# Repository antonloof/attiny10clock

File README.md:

# attiny10clock
How to not make a clock. 
test

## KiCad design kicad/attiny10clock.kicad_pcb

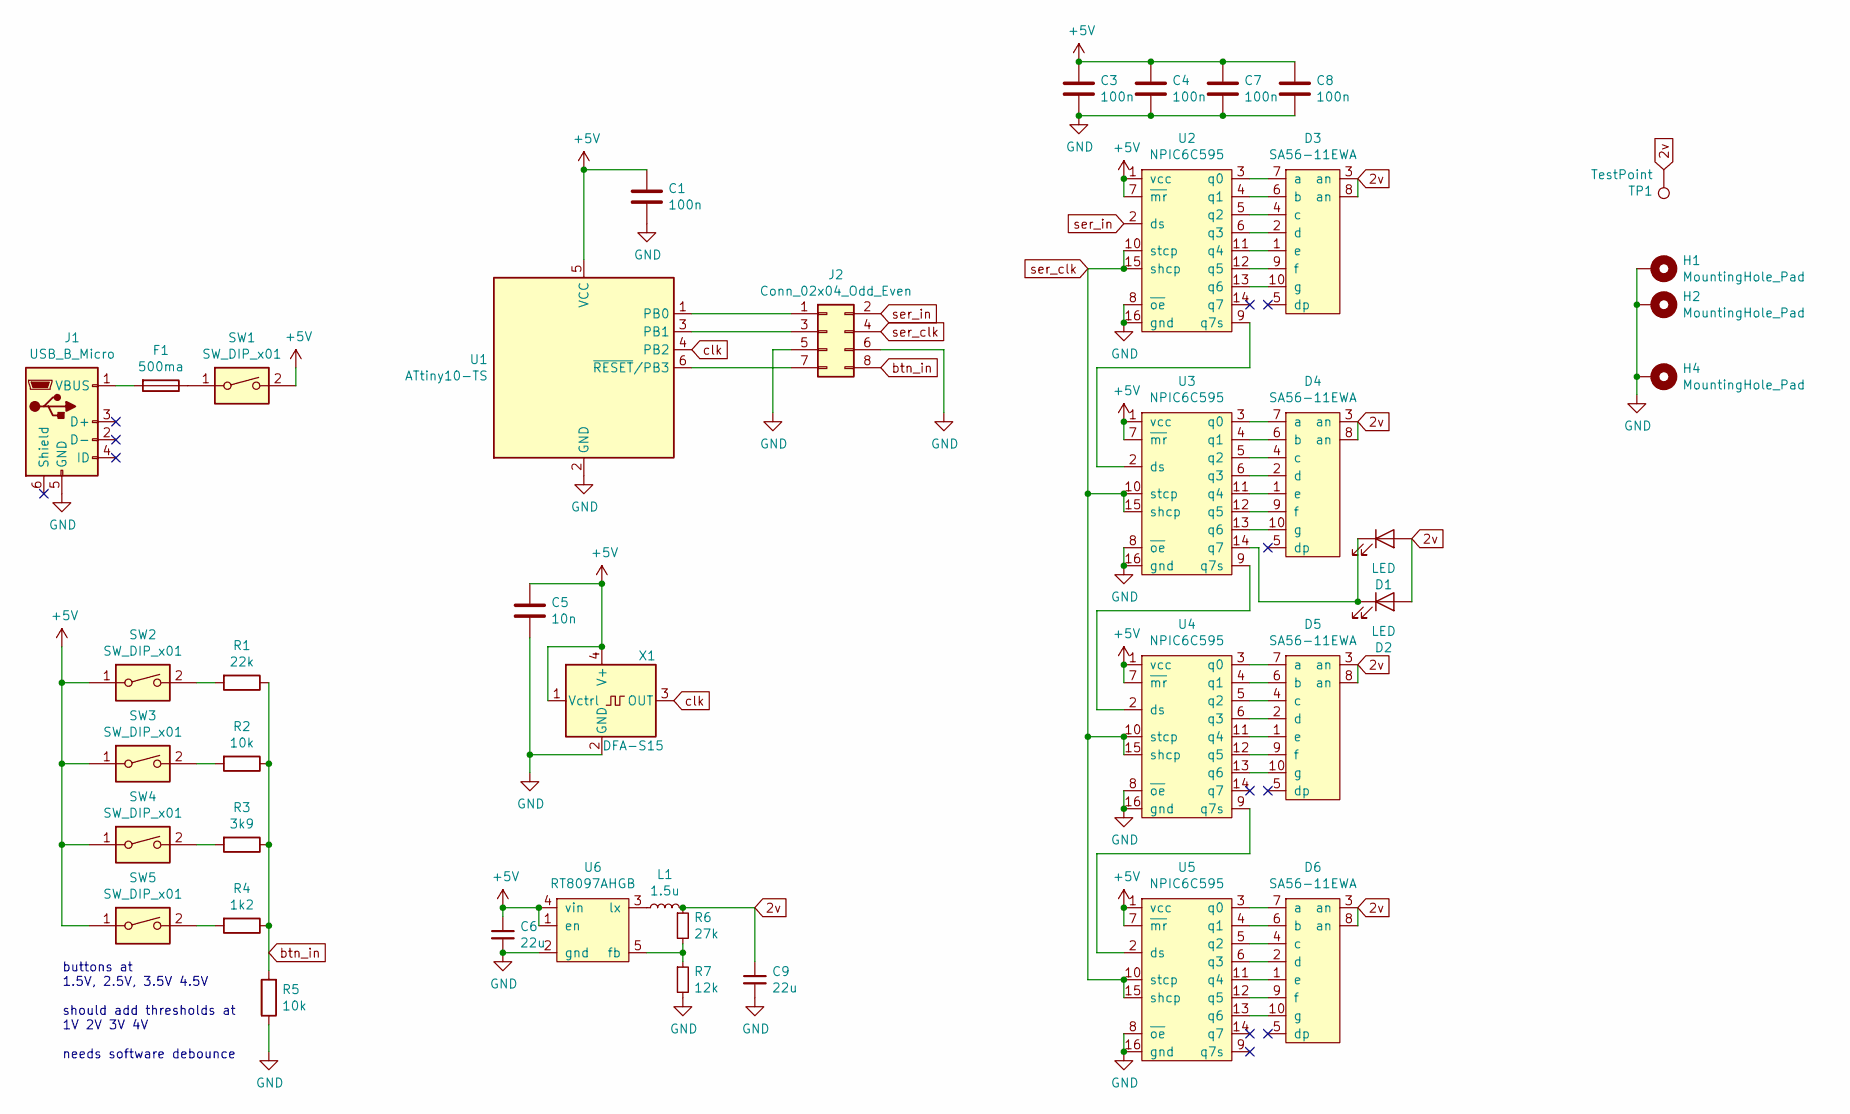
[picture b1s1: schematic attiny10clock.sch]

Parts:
C1, C3, C4, C7, C8: 100n; C_0805_2012Metric_Pad1.15x1.40mm_HandSolder
C5: 10n; C_0805_2012Metric_Pad1.15x1.40mm_HandSolder
C6, C9: 22u; C_0805_2012Metric_Pad1.15x1.40mm_HandSolder
D1, D2: LED; LED_D5.0mm
D3, D4, D5, D6: SA56-11EWA; DIP-10_600_ELL
F1: 500ma; Fuse_1206_3216Metric_Pad1.42x1.75mm_HandSolder
H1, H2, H4: MountingHole_Pad; MountingHole_2.2mm_M2_Pad
J1: USB_B_Micro; USB_MICRO_10118193-0001LF
J2: Conn_02x04_Odd_Even; PinHeader_2x04_P2.54mm_Vertical
L1: 1.5u; L_Wuerth_WE-PD-Typ-7345
R1: 22k; R_0603_1608Metric_Pad1.05x0.95mm_HandSolder
R2, R5: 10k; R_0603_1608Metric_Pad1.05x0.95mm_HandSolder
R3: 3k9; R_0603_1608Metric_Pad1.05x0.95mm_HandSolder
R4: 1k2; R_0603_1608Metric_Pad1.05x0.95mm_HandSolder
R6: 27k; R_0603_1608Metric_Pad1.05x0.95mm_HandSolder
R7: 12k; R_0603_1608Metric_Pad1.05x0.95mm_HandSolder
SW1: SW_DIP_x01; PinHeader_1x02_P2.54mm_Vertical
SW2, SW3, SW4, SW5: SW_DIP_x01; SW_Cherry_MX_1.00u_Plate
TP1: TestPoint; TestPoint_Pad_D2.0mm
U1: ATtiny10-TS; SOT-23-6
U2, U3, U4, U5: NPIC6C595; TSSOP-16_4.4x5mm_P0.65mm
U6: RT8097AHGB; SOT-23-5_HandSoldering
X1: DFA-S15; ASFLK

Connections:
2v: C9.1, D1.2 (A), D2.2 (A), D3.3 (an), D3.8 (an), D4.3 (an), D4.8 (an), D5.3 (an), D5.8 (an), D6.3 (an), D6.8 (an), L1.2, R6.1, TP1.1; also elsewhere on the board
+5V: C1.1, C3.1, C4.1, C5.1, C6.1, C7.1, C8.1, SW1.2, SW2.1, SW3.1, SW4.1, SW5.1, U1.5 (VCC), U2.1 (vcc), U2.7 (~mr), U3.1 (vcc), U3.7 (~mr), U4.1 (vcc), U4.7 (~mr), U5.1 (vcc), U5.7 (~mr), U6.1 (en), U6.4 (vin), X1.1 (Vctrl), X1.4 (V+)
GND: C1.2, C3.2, C4.2, C5.2, C6.2, C7.2, C8.2, C9.2, H1.1, H2.1, H4.1, J1.5 (GND), J2.5, J2.6, R5.1, R7.2, U1.2 (GND), U2.8 (~oe), U2.16 (gnd), U3.8 (~oe), U3.16 (gnd), U4.8 (~oe), U4.16 (gnd), U5.8 (~oe), U5.16 (gnd), U6.2 (gnd), X1.2 (GND)
unnamed: D1.1 (K), D2.1 (K), U3.14 (q7)
unnamed: D3.1 (e), U2.11 (q4)
unnamed: D3.2 (d), U2.6 (q3)
unnamed: D3.4 (c), U2.5 (q2)
unnamed: D3.6 (b), U2.4 (q1)
unnamed: D3.7 (a), U2.3 (q0)
unnamed: D3.9 (f), U2.12 (q5)
unnamed: D3.10 (g), U2.13 (q6)
unnamed: D4.1 (e), U3.11 (q4)
unnamed: D4.2 (d), U3.6 (q3)
unnamed: D4.4 (c), U3.5 (q2)
unnamed: D4.6 (b), U3.4 (q1)
unnamed: D4.7 (a), U3.3 (q0)
unnamed: D4.9 (f), U3.12 (q5)
unnamed: D4.10 (g), U3.13 (q6)
unnamed: D5.1 (e), U4.11 (q4)
unnamed: D5.2 (d), U4.6 (q3)
unnamed: D5.4 (c), U4.5 (q2)
unnamed: D5.6 (b), U4.4 (q1)
unnamed: D5.7 (a), U4.3 (q0)
unnamed: D5.9 (f), U4.12 (q5)
unnamed: D5.10 (g), U4.13 (q6)
unnamed: D6.1 (e), U5.11 (q4)
unnamed: D6.2 (d), U5.6 (q3)
unnamed: D6.4 (c), U5.5 (q2)
unnamed: D6.6 (b), U5.4 (q1)
unnamed: D6.7 (a), U5.3 (q0)
unnamed: D6.9 (f), U5.12 (q5)
unnamed: D6.10 (g), U5.13 (q6)
unnamed: F1.1, SW1.1
unnamed: F1.2, J1.1 (VBUS)
unnamed: J2.1, U1.1 (PB0)
unnamed: J2.3, U1.3 (PB1)
unnamed: J2.7, U1.6 (~RESET~/PB3)
unnamed: L1.1, U6.3 (lx)
unnamed: R1.2, SW2.2
unnamed: R2.2, SW3.2
unnamed: R3.2, SW4.2
unnamed: R4.2, SW5.2
unnamed: R6.2, R7.1, U6.5 (fb)
unnamed: U2.9 (q7s), U3.2 (ds)
unnamed: U3.9 (q7s), U4.2 (ds)
unnamed: U4.9 (q7s), U5.2 (ds)
btn_in: J2.8, R1.1, R2.1, R3.1, R4.1, R5.2
clk: U1.4 (PB2), X1.3 (OUT)
ser_clk: J2.4, U2.10 (stcp), U2.15 (shcp), U3.10 (stcp), U3.15 (shcp), U4.10 (stcp), U4.15 (shcp), U5.10 (stcp), U5.15 (shcp)
ser_in: J2.2, U2.2 (ds)

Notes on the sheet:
buttons at 1.5V, 2.5V, 3.5V 4.5V should add thresholds at 1V 2V 3V 4V needs software debounce

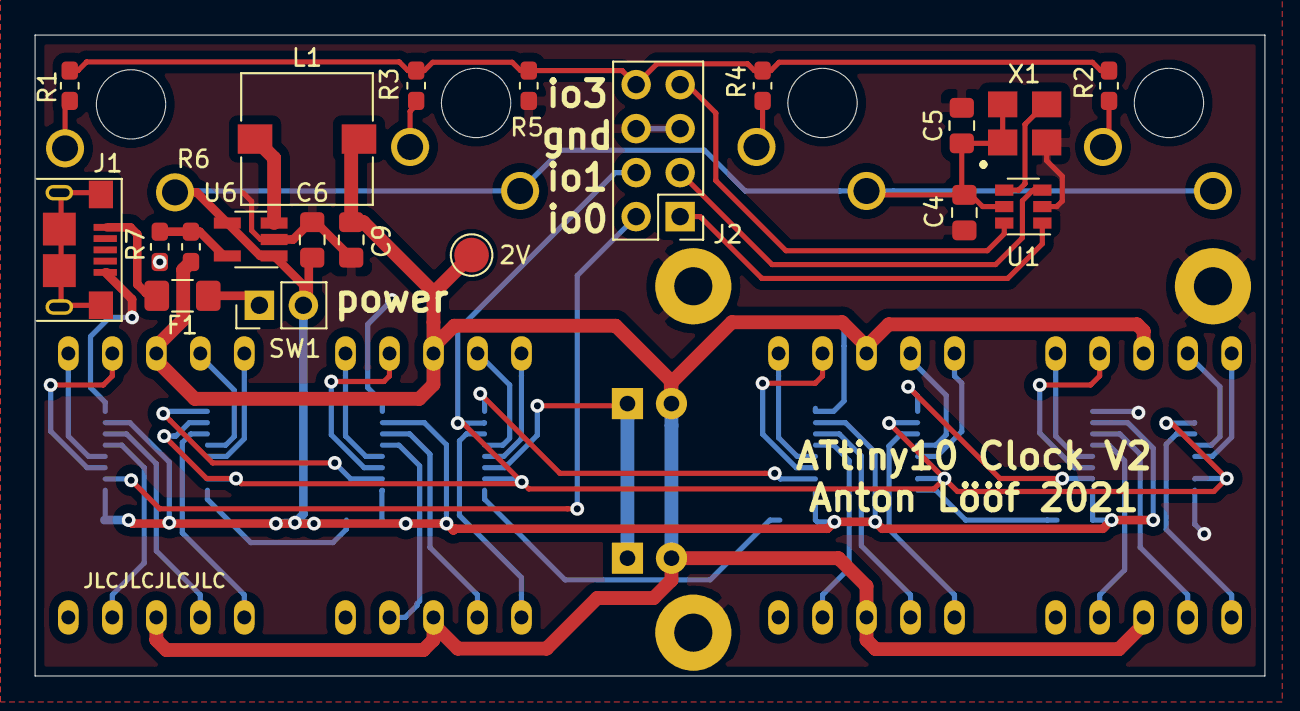
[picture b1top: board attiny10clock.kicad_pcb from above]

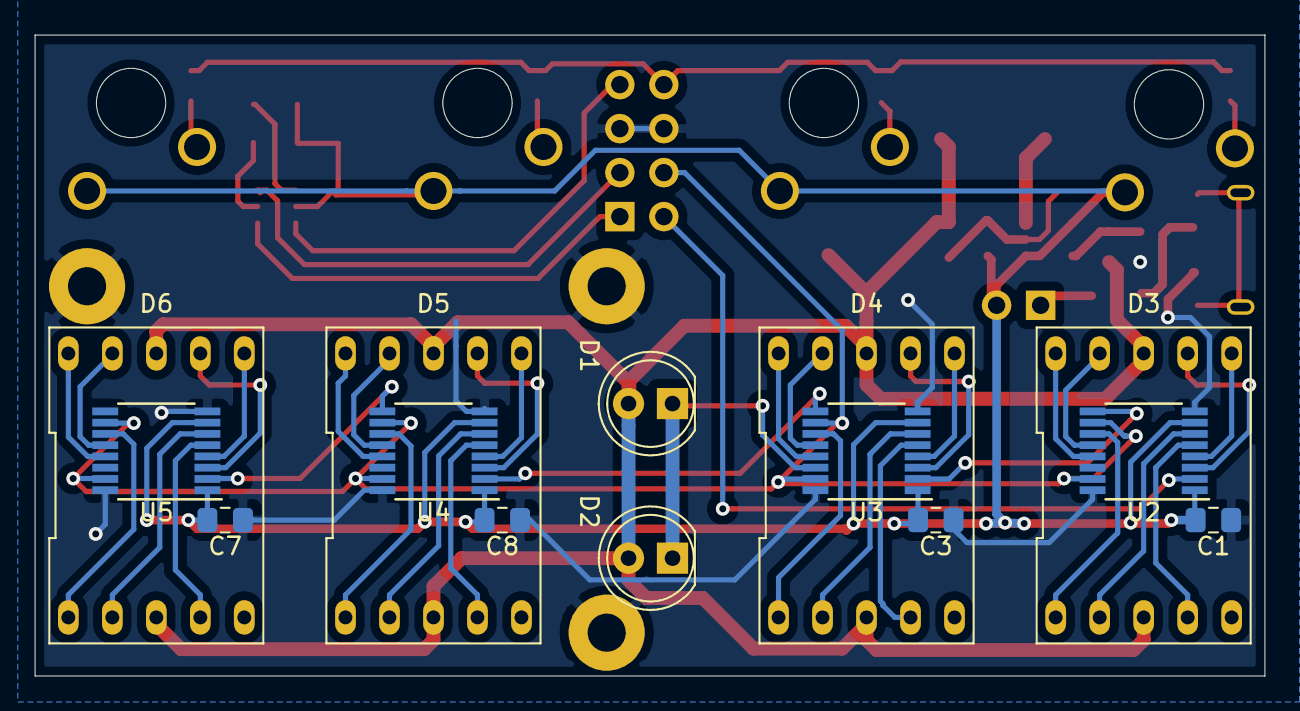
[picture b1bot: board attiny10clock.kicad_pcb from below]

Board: 2 copper layers, 71.0 x 37.0 mm, 41 parts (18 on the bottom side), 50 nets.

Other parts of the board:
2V: TestPoint; TestPoint_Pad_D2.0mm

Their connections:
2v: 2V.1; also elsewhere on the board

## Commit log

2021-02-17 Add hardware v1
2021-02-17 test pcb change
2021-02-17 test
2021-02-18 Add untested initial code :D
2021-02-18 Init some values
2021-02-19 Move stuff
2021-02-21 use different footpritn for osc
2021-02-21 experiment with hardware a bit :D
2021-02-25 It be showing time now
2021-03-07 Rev 3 of schematic, start pcb
    also new code rev
2021-03-13 Úse another buck converter
2021-03-14 Use new micro usb + more routing
2021-03-15 Finalize rev 2 pcb
2021-03-17 Add back silk screan on backside
2021-04-21 Enable interrupt
2021-04-30 Yey hardware works
2021-05-03 Lower led voltage
2021-05-04 add btn logic
    untested, goto eta plz
    dont work on martins MT stupid
    test your clock
2021-05-06 Code is DONW
